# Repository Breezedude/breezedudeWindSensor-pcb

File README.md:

# breezedudeWindSensor-pcb
PCB of Breezedude Wind Sensor Transmitter

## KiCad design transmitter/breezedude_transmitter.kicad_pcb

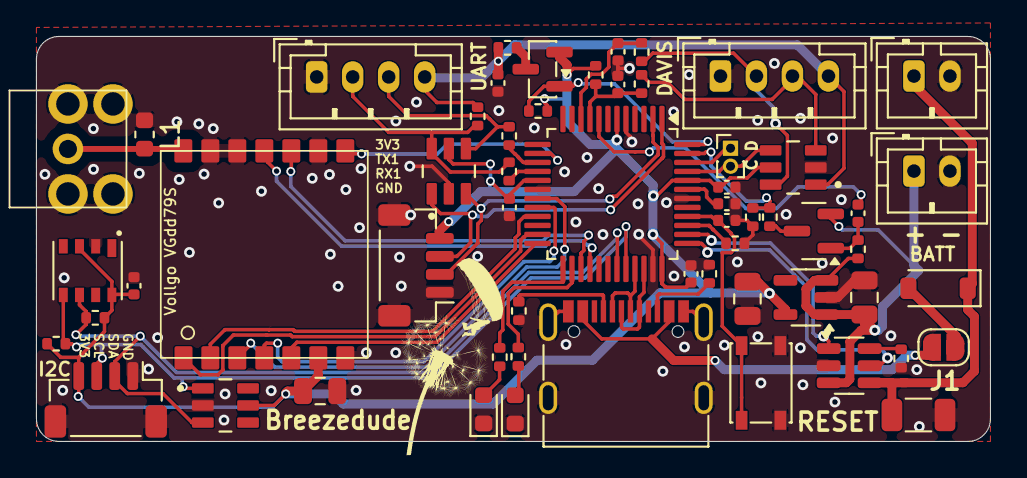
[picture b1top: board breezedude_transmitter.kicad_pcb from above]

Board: 2 copper layers, 53.0 x 22.5 mm, 59 parts (1 on the bottom side), 50 nets.

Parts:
AE1: Antenna_Shield; sma_edge_6.5mm_vert
BT1: 1050; BAT_1050
C1: 47u 10V; C_1206_3216Metric
C2, C6, C8: 10u 6.3V; C_0402_1005Metric
C3, C4, C12: 47u 6.3V; C_0805_2012Metric
C5, C9, C10, C11, C13, C14: 100n 16V; C_0402_1005Metric
C7: 10n 16V; C_0402_1005Metric
D3: LED blue; LED_0603_1608Metric
D4: LED red; LED_0603_1608Metric
D5: Diode; D_SOD-123
J1, J6: Conn_01x02_Pin; JST_PH_B2B-PH-K_1x02_P2.00mm_Vertical
J2, J11: Conn_01x04_Pin; JST_SH_BM04B-SRSS-TB_1x04-1MP_P1.00mm_Vertical
J3, J5: Conn_01x04_Pin; JST_PH_B4B-PH-K_1x04_P2.00mm_Vertical
J7: USB_C_Receptacle_USB2.0_16P; USB_C_Receptacle_G-Switch_GT-USB-7010ASV
J8: Conn_01x02_Pin; PinHeader_1x02_P1.00mm_Vertical
JP1: SolderJumper_2_Open; SolderJumper-2_P1.3mm_Open_RoundedPad1.0x1.5mm
L1: 68nH; L_0603_1608Metric
Q2, Q3: P-MOS; SOT-23
R1, R3, R12: 10k; R_0402_1005Metric
R2, R5: 100k; R_0402_1005Metric
R4: 330k; R_0402_1005Metric
R6: 470; R_0402_1005Metric
R7: 200; R_0402_1005Metric
R8, R9: 3.3k; R_0402_1005Metric
R10, R11: 5.1k; R_0402_1005Metric
R13, R19: 4k7; R_0402_1005Metric
R14, R16, R17: 22R; R_0402_1005Metric
R15: 1k; R_0402_1005Metric
R18: 1M5; R_0402_1005Metric
SW1: SW_Push; SW_SPST_PTS810
U1, U10, U11: D1213A-04TS-7; SOT95P280X140-6N
U2: STLQ015M33R; SOT-23-5
U3: ATSAMD21G18A-A; TQFP-48_7x7mm_P0.5mm
U6: vollgo_vgdd79s868n0s1
U8: HP203B; HP203B-LGA8
U9: TP4057; TSOT-23-6

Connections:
3V3: C4.2, C6.2, C8.2, C10.2, C12.2, C14.2, J2.4, J11.4, Q3.2 (S), R2.1, R8.2, R9.2, R18.2, U1.5 (VP), U2.5 (VOUT), U3.6 (VDDANA), U3.17 (VDDIO), U3.36 (VDDIO), U3.44 (VDDIN), U6.6 (VCC), U8.3 (VDD), U8.8 (CSB), U10.5 (VP), U11.5 (VP)
/ANT: AE1.1 (A), L1.2, U6.14 (ANT)
/BATT+: BT1.P, C3.2, J1.1, Q2.2 (S), R3.1, U2.1 (VIN), U2.3 (EN), U9.3 (BAT)
/DAVIS_DIR: J3.2, R13.1, U1.6 (IO4)
/DAVIS_DIR_FILT: C7.2, R13.2, U3.10 (PA05)
/DAVIS_SPEED: J3.3, R15.2, U1.3 (IO2)
/DAVIS_SPEED_FILT: C5.1, R2.2, R15.1, U3.9 (PA04)
/HW_Ver1: R19.1, U3.39 (PA27)
/LED1: R6.1, U3.26 (PA17)
/LED2: R7.1, U3.25 (PA16)
/LORA_CS: U3.24 (PA15), U6.5 (CS)
/LORA_DIO1: U3.27 (PA18), U6.10 (DIO1)
/LORA_DIO2: U3.28 (PA19), U6.11 (BUSY)
/LORA_DIO3: U3.14 (PA09), U6.8 (DIO3)
/LORA_MISO: U3.21 (PA12), U6.2 (MISO)
/LORA_MOSI: U3.19 (PB10), U6.3 (MOSI)
/LORA_RESET: U3.23 (PA14), U6.1 (RST)
/LORA_SCK: U3.20 (PB11), U6.4 (SCK)
/PV_CHARGE: U3.38 (PB23), U9.1 (~CHRG)
/PV_DONE: U3.37 (PB22), U9.5 (STDBY)
/RESET: C11.2, SW1.1, U3.40 (~RESET)
/RX: J5.2, R12.1, R17.2, U11.6 (IO4)
/RX1: J11.2, U3.2 (PA01), U11.3 (IO2)
/SCL: J2.3, R8.1, U3.32 (PA23), U8.5 (SCL), U10.1 (IO1)
/SDA: J2.2, R9.1, U3.31 (PA22), U8.6 (SDA), U10.3 (IO2)
/SOLAR+: C1.2, D5.1 (K), J6.1, U9.4 (V_{CC})
/SWDCLK: J8.2, U1.4 (IO3), U3.45 (PA30)
/SWDIO: J8.1, U3.46 (PA31)
/SW_SENSOR: Q3.1 (G), R18.1, U3.48 (PB03)
/TX: J5.3, R16.2, U11.4 (IO3)
/TX1: J11.3, U3.1 (PA00), U11.1 (IO1)
/USB_N: J7.A7 (D-), J7.B7 (D-), U3.33 (PA24)
/USB_P: J7.A6 (D+), J7.B6 (D+), U3.34 (PA25)
/VCC_SENSOR: C13.2, J3.4, J5.4, R12.2, R14.1, U1.1 (IO1)
/V_DIV: R4.2, R5.1, U3.47 (PB02)
/V_IMP: C9.2, U3.8 (PB09)
GND: AE1.2 (Shield), BT1.N, C1.1, C2.1, C3.1, C4.1, C5.2, C6.1, C7.1, C8.1, C10.1, C11.1, C12.1, C13.1, C14.1, D3.1 (K), D4.1 (K), J1.2, J2.1, J2.MP (MountPin), J3.1, J5.1, J6.2, J7.A1 (GND), J7.A12 (GND), J7.B1 (GND), J7.B12 (GND), J7.S1 (SHIELD), J11.1, J11.MP (MountPin), L1.1, R1.2, R5.2, R10.2, R11.2, R19.2, SW1.2, U1.2 (VN), U2.2 (GND), U3.5 (GNDANA), U3.18 (GND), U3.35 (GND), U3.42 (GND), U6.7 (GND), U6.9 (GND), U6.12 (GND), U6.13 (GND), U8.2 (GND), U9.2 (GND), U10.2 (VN), U11.2 (VN)
unnamed: D3.2 (A), R6.2
unnamed: D4.2 (A), R7.2
unnamed: D5.2 (A), JP1.2 (B)
unnamed: J7.A5 (CC1), R10.1
unnamed: J7.B5 (CC2), R11.1
unnamed: J7.A4 (VBUS), J7.A9 (VBUS), J7.B4 (VBUS), J7.B9 (VBUS), JP1.1 (A)
unnamed: Q2.3 (D), R4.1
unnamed: C9.1, Q2.1 (G), R3.2
unnamed: Q3.3 (D), R14.2
unnamed: R16.1, U3.15 (PA10)
unnamed: R17.1, U3.16 (PA11)
unnamed: C2.2, U3.43 (VDDCORE)
unnamed: R1.1, U9.6 (PROG)

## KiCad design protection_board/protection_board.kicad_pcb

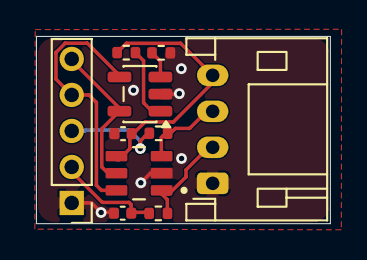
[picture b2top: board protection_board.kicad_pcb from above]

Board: 2 copper layers, 16.3 x 10.4 mm, 10 parts (0 on the bottom side), 10 nets.

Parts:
C7: 10n 16V; C_0402_1005Metric
C14: 100n 16V; C_0402_1005Metric
J3: Conn_01x04_Pin; JST_PH_S4B-PH-K_1x04_P2.00mm_Horizontal
J4: Conn_01x05_Pin; PinHeader_1x05_P2.00mm_Vertical
R13: 4.7k; R_0402_1005Metric
R15: 1k; R_0402_1005Metric
R16: 22R; R_0402_1005Metric
R17: 68k; R_0402_1005Metric
U1: AAT4610BIGV-1-T1; SOT-23-5
U2: D1213A-04TS-7; SOT95P280X140-6N

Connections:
/3V3: J4.5, U1.5 (IN), U2.5 (VP)
/DAVIS_DIR: J3.2, R13.1, U2.1 (IO1)
/DAVIS_DIR_FILT: C7.2, J4.2, R13.2
/DAVIS_SPEED: J3.3, R15.2, U2.3 (IO2)
/DAVIS_SPEED_FILT: J4.3, R15.1
/SW_POW: J4.4, U1.4 (ON), U2.6 (IO4)
/VCC_SENSOR: C14.2, J3.4, R16.1, U2.4 (IO3)
GND: C7.1, C14.1, J3.1, J4.1, R17.1, U1.2 (GND), U2.2 (VN)
unnamed: R16.2, U1.1 (OUT)
unnamed: R17.2, U1.3 (SET)

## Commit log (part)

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2026-06-05 V2.4 - see changelog

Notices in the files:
transmitter/breezedude_transmitter.kicad_pcb:
© Breezedude
